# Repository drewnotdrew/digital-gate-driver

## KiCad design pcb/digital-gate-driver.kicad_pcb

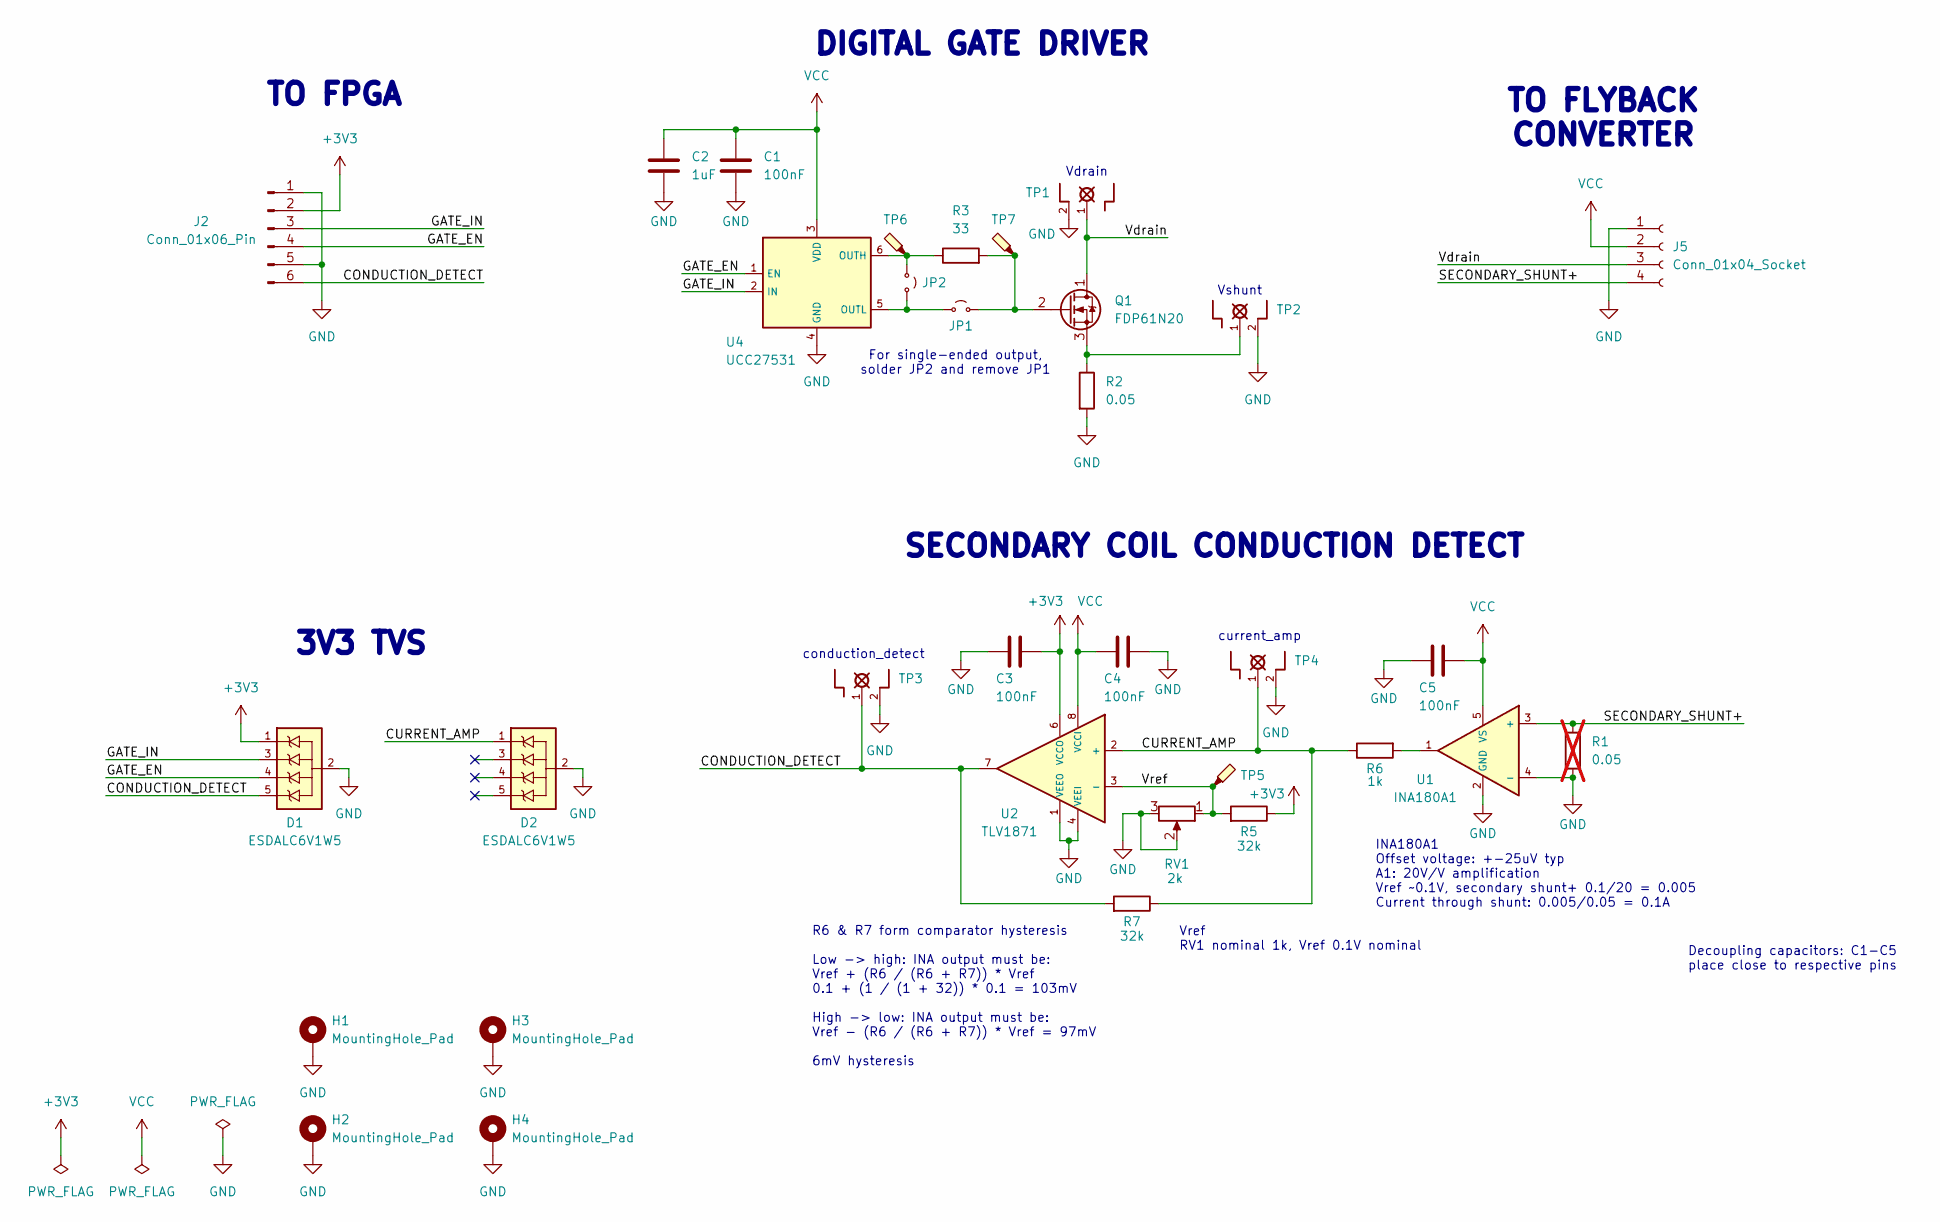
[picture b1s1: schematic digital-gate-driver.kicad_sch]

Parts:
C1, C3, C4, C5: 100nF; C_0603_1608Metric
C2: 1uF; C_0603_1608Metric
D1, D2: ESDALC6V1W5; MPN ESDALC6V1W5
H1, H2, H3, H4: MountingHole_Pad; MountingHole_2.5mm_Pad_Via
J2: Conn_01x06_Pin; PinHeader_1x06_P2.54mm_Vertical
J5: Conn_01x04_Socket; MOLEX_436500418
JP1, JP2: Jumper_2_Small_Open; SolderJumper-2_Open_Hooks0.8x1.8mm
Q1: FDP61N20; MPN FDP61N20
R1: 0.05; R_1206_3216Metric; not fitted
R2: 0.05; R_1206_3216Metric
R3: 33; THT_SOCKET_RESISTOR
R5, R7: 32k; R_0603_1608Metric
R6: 1k; R_0603_1608Metric
RV1: 2k; PV36W201C01B00
TP1, TP2, TP3, TP4: TP_SCOPE
TP5, TP6, TP7: TestPoint_Probe; TP_SMD
U1: INA180A1; INA180A1IDBVR; MPN INA180A1IDBVR
U2: TLV1871; TLV1871DDFR; MPN TLV1871DDFR
U4: UCC27531; UCC2753DBVT; MPN UCC27531DBVR

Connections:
+3V3: C3.2, D1.1, J2.2, R5.1, U2.6 (VCCO)
/CONDUCTION_DETECT: D1.5, J2.6, R7.2, TP3.1, U2.7
/CURRENT_AMP: D2.1, R6.1, R7.1, TP4.1, U2.2 (+)
/GATE_EN: D1.4, J2.4, U4.1 (EN)
/GATE_IN: D1.3, J2.3, U4.2 (IN)
/SECONDARY_SHUNT+: J5.4, R1.1, U1.3 (+)
/Vdrain: J5.3, Q1.1 (D), TP1.1
/Vref: R5.2, RV1.1, TP5.1, U2.3 (-)
GND: C1.2, C2.2, C3.1, C4.2, C5.1, D1.2, D2.2, H1.1, H2.1, H3.1, H4.1, J2.1, J2.5, J5.1, R1.2, R2.2, RV1.2, RV1.3, TP1.2, TP2.2, TP3.2, TP4.2, U1.2 (GND), U1.4 (-), U2.1 (VEEO), U2.4 (VEEI), U4.4 (GND)
unnamed: JP1.1 (A), JP2.2 (B), U4.5 (OUTL)
unnamed: JP1.2 (B), Q1.2 (G), R3.2, TP7.1
unnamed: JP2.1 (A), R3.1, TP6.1, U4.6 (OUTH)
unnamed: Q1.3 (S), R2.1, TP2.1
unnamed: R6.2, U1.1
VCC: C1.1, C2.1, C4.1, C5.2, J5.2, U1.5 (VS), U2.8 (VCCI), U4.3 (VDD)

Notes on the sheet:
conduction_detect
Decoupling capacitors: C1-C5 place close to respective pins
TO FLYBACK CONVERTER
3V3 TVS
For single-ended output, solder JP2 and remove JP1
DIGITAL GATE DRIVER
INA180A1 Offset voltage: +-25uV typ A1: 20V/V amplification Vref ~0.1V, secondary shunt+ 0.1/20 = 0.005 Current through shunt: 0.005/0.05 = 0.1A
Vref RV1 nominal 1k, Vref 0.1V nominal
Vshunt
R6 & R7 form comparator hysteresis Low -> high: INA output must be: Vref + (R6 / (R6 + R7)) * Vref 0.1 + (1 / (1 + 32)) * 0.1 = 103mV High -> low: INA output must be: Vref - (R6 / (R6 + R7)) * Vref = 97mV 6mV hysteresis
SECONDARY COIL CONDUCTION DETECT
current_amp
Vdrain
TO FPGA

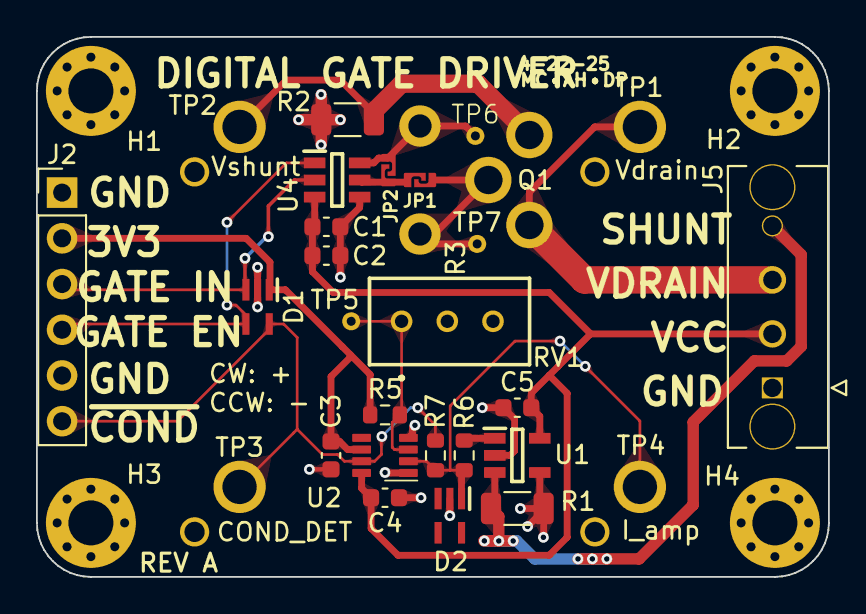
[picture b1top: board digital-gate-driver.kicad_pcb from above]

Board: 2 copper layers, 44.0 x 30.0 mm, 33 parts (0 on the bottom side), 15 nets.

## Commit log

2025-04-19 add blank readme
2025-04-19 setup env, add uart ip
2025-04-19 update setup script
2025-04-19 add gitignore
2025-04-19 add blank dgd pcb
2025-04-20 organize files
2025-04-20 add lab util
2025-04-20 update deps
2025-04-20 add dgd selection documentation
2025-04-21 add block diagram
2025-04-21 update gitignore
2025-04-21 add parts to symbol lib
2025-04-21 complete base schematic
2025-04-21 complete schematic, assign all fp
2025-04-21 update header fp
2025-04-21 update shunt resistor sizes
2025-04-22 add all footprints
2025-04-23 complete layout
2025-04-23 spec hysteresis resistors, update socket hole diameters
2025-04-23 add fab files
2025-04-23 add final fab files
2025-04-24 fix path to spar script
2025-04-24 fix path to logs
2025-04-27 Fix makefile and add starter files
2025-04-30 Add test files
2025-05-02 Add pwm testbench files
2025-05-02 Add makefile
2025-05-02 Add pwm module
2025-05-02 debug pwm
2025-05-02 Edit pwm module
2025-05-02 Finalize PWM module
